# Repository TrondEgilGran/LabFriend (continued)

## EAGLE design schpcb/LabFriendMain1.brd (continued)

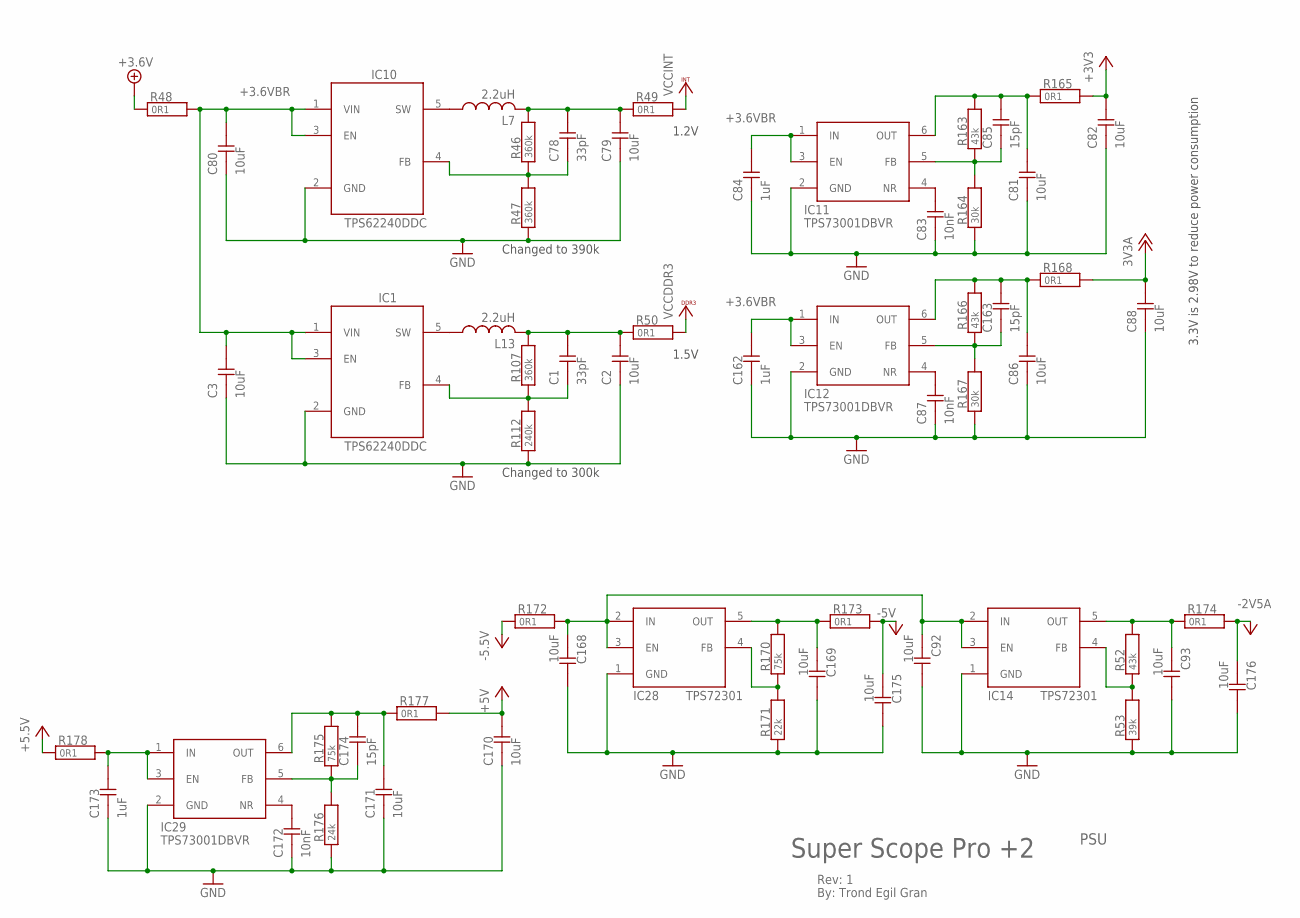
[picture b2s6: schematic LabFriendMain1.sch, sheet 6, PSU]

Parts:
C1, C78: 33pF; 0603
C2, C3, C79, C80, C81, C82, C86, C88, C92, C93, C168, C169, C170, C171, C175, C176: 10uF; 0603
C83, C87, C172: 10nF; 0402
C84, C162, C173: 1uF; 0603
C85, C163, C174: 15pF; 0603
IC1, IC10: TPS62240DDC; SOT23-5L
IC11, IC12, IC29: TPS73001DBVR; SOT23-6L
IC14, IC28: TPS72301; SOT23-5L
L7, L13: 2.2uH; L3216C
R46, R47, R107: 360k; 0603
R48, R49, R50, R165, R168, R172, R173, R174, R177, R178: 0R1; 0603
R52, R163, R166: 43k; 0603
R53: 39k; 0603
R112: 240k; 0603
R164, R167: 30k; 0603
R170, R175: 75k; 0603
R171: 22k; 0603
R176: 24k; 0603

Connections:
3V3A: C88.2, R168.2; also elsewhere on the board
+3.6V: R48.1; also elsewhere on the board
+3.6VBR: C3.2, C80.2, C84.2, C162.2, IC1.1 (VIN), IC1.3 (EN), IC10.1 (VIN), IC10.3 (EN), IC11.1 (IN), IC11.3 (EN), IC12.1 (IN), IC12.3 (EN), R48.2
+3V3: C82.2, R165.2; also elsewhere on the board
+5.5V: R178.1; also elsewhere on the board
+5.5VI: C173.2, IC29.1 (IN), IC29.3 (EN), R178.2
+5V: C170.2, R177.2; also elsewhere on the board
-2.5VI: C93.1, IC14.5 (OUT), R52.2, R174.1
-2V5A: C176.1, R174.2; also elsewhere on the board
-5.5V: R172.1; also elsewhere on the board
-5V: C175.1, R173.2; also elsewhere on the board
GND: C2.1, C3.1, C79.1, C80.1, C81.1, C82.1, C83.1, C84.1, C86.1, C87.1, C88.1, C92.2, C93.2, C162.1, C168.2, C169.2, C170.1, C171.1, C172.1, C173.1, C175.2, C176.2, IC1.2 (GND), IC10.2 (GND), IC11.2 (GND), IC12.2 (GND), IC14.1 (GND), IC28.1 (GND), IC29.2 (GND), R47.1, R53.1, R112.1, R164.1, R167.1, R171.1, R176.1; also elsewhere on the board
unnamed: C83.2, IC11.4 (NR)
unnamed: C78.1, IC10.4 (FB), R46.1, R47.2
unnamed: IC14.4 (FB), R52.1, R53.2
unnamed: IC10.5 (SW), L7.1
unnamed: C92.1, C168.1, IC14.2 (IN), IC14.3 (EN), IC28.2 (IN), IC28.3 (EN), R172.2
unnamed: C78.2, C79.2, L7.2, R46.2, R49.1
unnamed: C87.2, IC12.4 (NR)
unnamed: C1.2, C2.2, L13.2, R50.1, R107.2
unnamed: C1.1, IC1.4 (FB), R107.1, R112.2
unnamed: IC1.5 (SW), L13.1
unnamed: C81.2, C85.2, IC11.6 (OUT), R163.2, R165.1
unnamed: C85.1, IC11.5 (FB), R163.1, R164.2
unnamed: C86.2, C163.2, IC12.6 (OUT), R166.2, R168.1
unnamed: C163.1, IC12.5 (FB), R166.1, R167.2
unnamed: C169.1, IC28.5 (OUT), R170.2, R173.1
unnamed: IC28.4 (FB), R170.1, R171.2
unnamed: C172.2, IC29.4 (NR)
unnamed: C171.2, C174.2, IC29.6 (OUT), R175.2, R177.1
unnamed: C174.1, IC29.5 (FB), R175.1, R176.2
VCCDDR3: R50.2; also elsewhere on the board
VCCINT: R49.2; also elsewhere on the board

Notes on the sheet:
Rev: 1
By: Trond Egil Gran
Super Scope Pro +2
PSU
3.3V is 2.98V to reduce power consumption
1.2V
1.5V
Changed to 300k
Changed to 390k

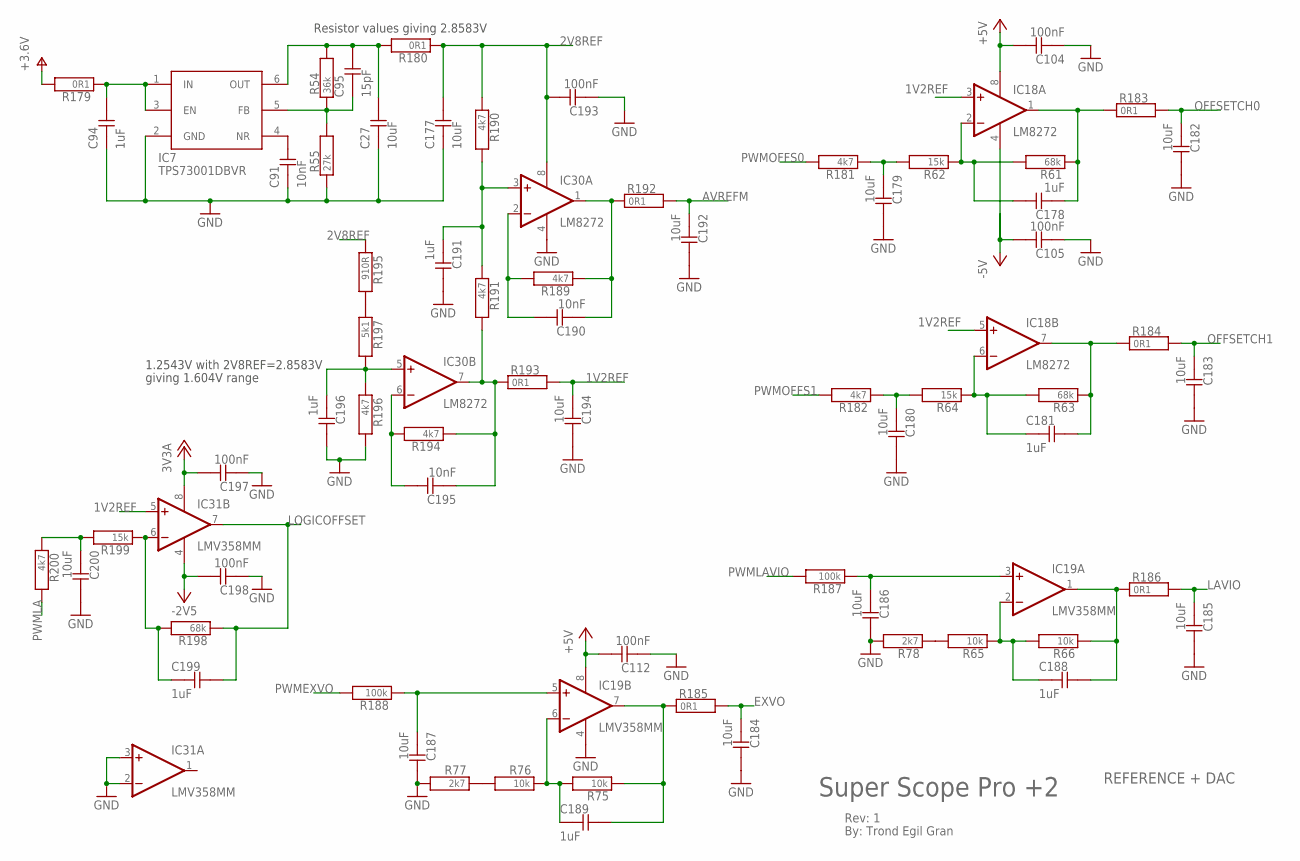
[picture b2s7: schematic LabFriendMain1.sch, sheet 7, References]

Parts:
C27, C177, C179, C180, C182, C183, C184, C185, C186, C187, C192, C194, C200: 10uF; 0603
C91, C190, C195: 10nF; 0402
C94, C178, C181, C188, C189, C191, C196, C199: 1uF; 0603
C95: 15pF; 0603
C104, C105, C112, C193, C197, C198: 100nF; 0402
IC7: TPS73001DBVR; SOT23-6L
IC18, IC30: LM8272; MSOP08
IC19, IC31: LMV358MM; MSOP08
R54: 36k; 0603
R55: 27k; 0603
R61, R63, R198: 68k; 0603
R62, R64, R199: 15k; 0603
R65, R66, R75, R76: 10k; 0603
R77, R78: 2k7; 0603
R179, R180, R183, R184, R185, R186, R192, R193: 0R1; 0603
R181, R182, R189, R190, R191, R194, R196, R200: 4k7; 0603
R187, R188: 100k; 0603
R195: 910R; 0603
R197: 5k1; 0603

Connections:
1V2REF: C194.1, IC18.3 (+IN), IC18.5 (+IN), IC31.5 (+IN), R193.2; also elsewhere on the board
2V8REF: C177.2, C193.2, IC30.8 (V+), R180.1, R190.1, R195.1; also elsewhere on the board
3V3A: C197.2, IC31.8 (V+); also elsewhere on the board
+3.6V: R179.2; also elsewhere on the board
+3.6VI: C94.2, IC7.1 (IN), IC7.3 (EN), R179.1
+5V: C104.2, C112.2, IC18.8 (V+), IC19.8 (V+); also elsewhere on the board
-2V5A: C198.2, IC31.4 (V-); also elsewhere on the board
-5V: C105.2, IC18.4 (V-); also elsewhere on the board
AVREFM: C192.1, R192.2; also elsewhere on the board
EXVO: C184.1, R185.2; also elsewhere on the board
EXVOI: C189.2, IC19.7 (OUT), R75.1, R185.1
GND: C27.1, C91.1, C94.1, C104.1, C105.1, C112.1, C177.1, C179.2, C180.2, C182.2, C183.2, C184.2, C185.2, C186.2, C187.2, C191.2, C192.2, C193.1, C194.2, C196.2, C197.1, C198.1, C200.2, IC7.2 (GND), IC19.4 (V-), IC30.4 (V-), IC31.2 (-IN), IC31.3 (+IN), R55.1, R77.2, R78.2, R196.2; also elsewhere on the board
LAVIO: C185.1, R186.2; also elsewhere on the board
LAVIOI: C188.2, IC19.1 (OUT), R66.1, R186.1
LOGICOFFSET: C199.2, IC31.7 (OUT), R198.1; also elsewhere on the board
unnamed: C191.1, IC30.3 (+IN), R190.2, R191.1
unnamed: C91.2, IC7.4 (NR)
unnamed: C188.1, IC19.2 (-IN), R65.1, R66.2
unnamed: C178.2, IC18.2 (-IN), R61.2, R62.1
unnamed: C27.2, C95.2, IC7.6 (OUT), R54.2, R180.2
unnamed: C181.1, IC18.6 (-IN), R63.2, R64.1
unnamed: C179.1, R62.2, R181.1
unnamed: C180.1, R64.2, R182.1
unnamed: C186.1, IC19.3 (+IN), R187.1
unnamed: C187.1, IC19.5 (+IN), R188.1
unnamed: R76.2, R77.1
unnamed: C95.1, IC7.5 (FB), R54.1, R55.2
unnamed: C189.1, IC19.6 (-IN), R75.2, R76.1
unnamed: R65.2, R78.1
unnamed: R195.2, R197.1
unnamed: C190.1, IC30.1 (OUT), R189.1, R192.1
unnamed: C190.2, IC30.2 (-IN), R189.2
unnamed: C195.1, IC30.7 (OUT), R191.2, R193.1, R194.1
unnamed: C195.2, IC30.6 (-IN), R194.2
unnamed: C196.1, IC30.5 (+IN), R196.1, R197.2
unnamed: C199.1, IC31.6 (-IN), R198.2, R199.1
unnamed: C200.1, R199.2, R200.1
OFFSETCH0: C182.1, R183.2; also elsewhere on the board
OFFSETCH0I: C178.1, IC18.1 (OUT), R61.1, R183.1
OFFSETCH1: C183.1, R184.2; also elsewhere on the board
OFFSETCH1I: C181.2, IC18.7 (OUT), R63.1, R184.1
PWMEXVO: R188.2; also elsewhere on the board
PWMLA: R200.2; also elsewhere on the board
PWMLAVIO: R187.2; also elsewhere on the board
PWMOFFS0: R181.2; also elsewhere on the board
PWMOFFS1: R182.2; also elsewhere on the board

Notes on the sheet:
Rev: 1
By: Trond Egil Gran
Super Scope Pro +2
REFERENCE + DAC
1.2543V with 2V8REF=2.8583V
giving 1.604V range
Resistor values giving 2.8583V

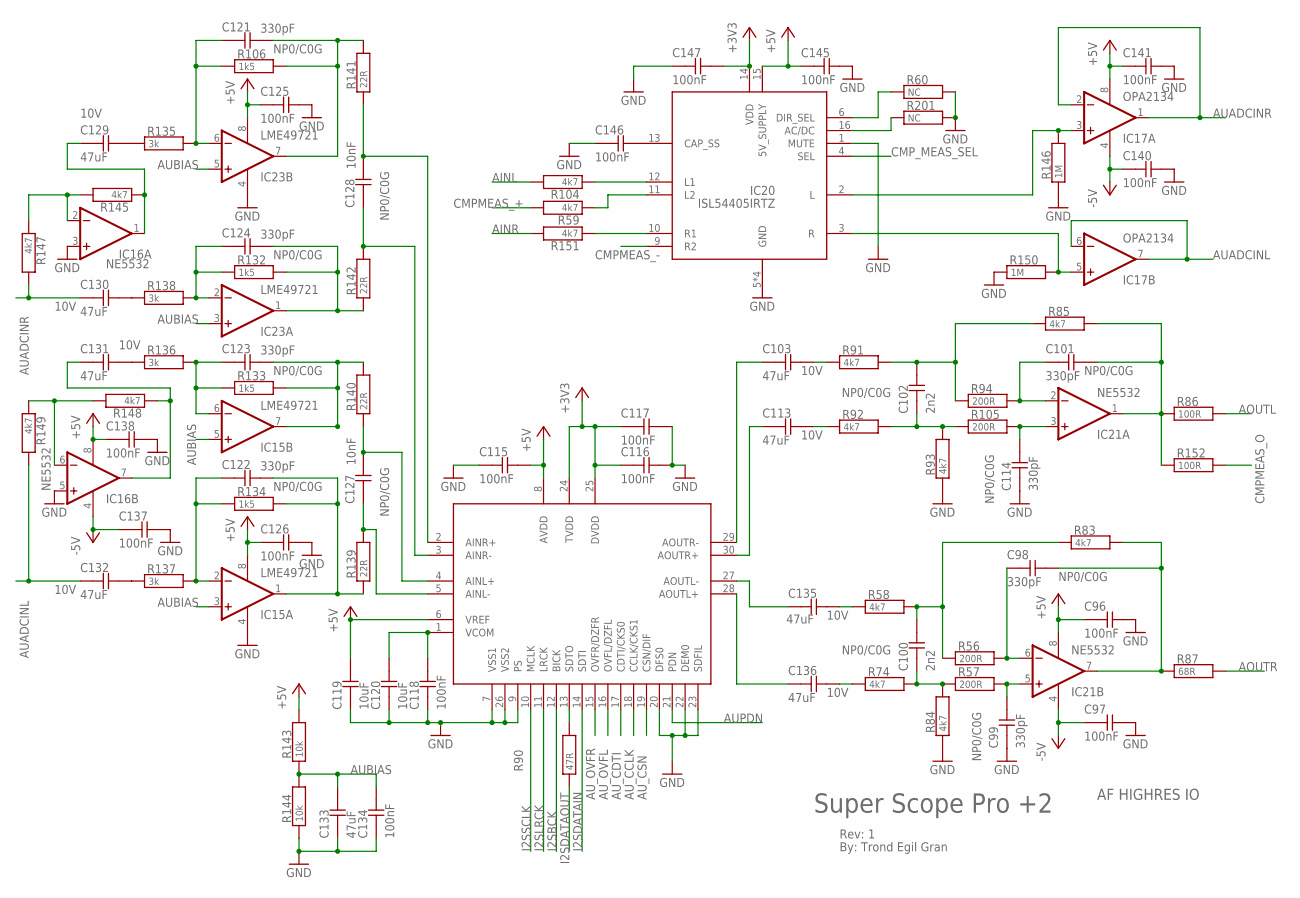
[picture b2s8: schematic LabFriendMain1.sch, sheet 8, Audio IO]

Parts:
C96, C97, C115, C116, C117, C118, C125, C126, C134, C137, C138, C140, C141, C145, C146, C147: 100nF; 0402
C98, C99, C101, C114, C121, C122, C123, C124: 330pF; 0603
C100, C102: 2n2; 0603
C103, C113, C129, C130, C131, C132, C133, C135, C136: 47uF; 1206; VOLTAGE 10V
C119, C120: 10uF; 0603
C127, C128: 10nF; 0603
IC13: AK4621; VSOP30
IC15, IC23: LME49721; SO08
IC16, IC21: NE5532; SO08
IC17: OPA2134; SO08
IC20: ISL54405IRTZ; TQFN3X3
R56, R57, R94, R105: 200R; 0603
R58, R59, R74, R83, R84, R85, R91, R92, R93, R104, R145, R147, R148, R149, R151: 4k7; 0603
R60, R201: NC; 0402
R86, R152: 100R; 0402
R87: 68R; 0603
R90: 47R; 0402
R106, R132, R133, R134: 1k5; 0603
R135, R136, R137, R138: 3k; 0603
R139, R140, R141, R142: 22R; 0603
R143, R144: 10k; 0603
R146, R150: 1M; 0603

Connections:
+3V3: C116.1, C117.1, C147.2, IC13.24 (TVDD), IC13.25 (DVDD), IC20.14 (VDD); also elsewhere on the board
+5V: C96.1, C115.2, C119.2, C125.1, C126.1, C138.1, C141.1, C145.1, IC13.6 (VREF), IC13.8 (AVDD), IC15.8 (V+), IC16.8 (V+), IC17.8 (V+), IC20.15 (5V_SUPPLY), IC21.8 (V+), IC23.8 (V+), R143.2; also elsewhere on the board
-5V: C97.1, C137.1, C140.1, IC16.4 (V-), IC17.4 (V-), IC21.4 (V-); also elsewhere on the board
AINL: R104.2; also elsewhere on the board
AINR: R151.2; also elsewhere on the board
AOUTL: R86.2; also elsewhere on the board
AOUTR: R87.2; also elsewhere on the board
AUADCINL: C132.1, IC17.6 (-IN), IC17.7 (OUT), R149.2
AUADCINR: C130.1, IC17.1 (OUT), IC17.2 (-IN), R147.2
AUBIAS: C133.2, C134.2, IC15.3 (+IN), IC15.5 (+IN), IC23.3 (+IN), IC23.5 (+IN), R143.1, R144.2
AUPDN: IC13.21 (PDN); also elsewhere on the board
AU_CCLK: IC13.18 (CCLK/CKS1); also elsewhere on the board
AU_CDTI: IC13.17 (CDTI/CKS0); also elsewhere on the board
AU_CSN: IC13.19 (CSN/DIF); also elsewhere on the board
AU_OVFL: IC13.16 (OVFL/DZFL); also elsewhere on the board
AU_OVFR: IC13.15 (OVFR/DZFR); also elsewhere on the board
CMPMEAS_+: R59.2; also elsewhere on the board
CMPMEAS_-: IC20.9 (R2); also elsewhere on the board
CMPMEAS_O: R152.2; also elsewhere on the board
CMP_MEAS_SEL: IC20.4 (SEL); also elsewhere on the board
GND: C96.2, C97.2, C99.1, C114.1, C115.1, C116.2, C117.2, C118.1, C119.1, C120.1, C125.2, C126.2, C133.1, C134.1, C137.2, C138.2, C140.2, C141.2, C145.2, C146.1, C147.1, IC13.7 (VSS1), IC13.9 (PS), IC13.20 (DFS0), IC13.22 (DEM0), IC13.23 (SDFIL), IC13.26 (VSS2), IC15.4 (V-), IC16.3 (+IN), IC16.5 (+IN), IC20.1 (MUTE), IC20.5 (GND), IC20.7 (GND), IC20.8 (GND), IC20.GPD (GND), IC23.4 (V-), R60.2, R84.1, R93.1, R144.1, R146.1, R150.1, R201.2; also elsewhere on the board
I2SBCK: IC13.12 (BICK); also elsewhere on the board
I2SDATAIN: IC13.14 (SDTI); also elsewhere on the board
I2SDATAOUT: R90.1; also elsewhere on the board
I2SLRCK: IC13.11 (LRCK); also elsewhere on the board
I2SSCLK: IC13.10 (MCLK); also elsewhere on the board
unnamed: C98.1, IC21.6 (-IN), R56.2
unnamed: C99.2, IC21.5 (+IN), R57.2
unnamed: C98.2, IC21.7 (OUT), R83.2, R87.1
unnamed: C100.2, R56.1, R58.2, R83.1
unnamed: C100.1, R57.1, R74.2, R84.2
unnamed: C135.2, R58.1
unnamed: C136.2, R74.1
unnamed: C101.2, IC21.1 (OUT), R85.2, R86.1, R152.1
unnamed: C101.1, IC21.2 (-IN), R94.2
unnamed: C114.2, IC21.3 (+IN), R105.2
unnamed: C102.2, R85.1, R91.2, R94.1
unnamed: C121.2, IC23.7 (OUT), R106.2, R141.2
unnamed: C102.1, R92.2, R93.2, R105.1
unnamed: C103.2, R91.1
unnamed: C113.2, R92.1
unnamed: C103.1, IC13.29 (AOUTR-)
unnamed: IC13.13 (SDTO), R90.2
unnamed: C113.1, IC13.30 (AOUTR+)
unnamed: C136.1, IC13.28 (AOUTL+)
unnamed: C135.1, IC13.27 (AOUTL-)
unnamed: C121.1, IC23.6 (-IN), R106.1, R135.2
unnamed: C124.2, IC23.1 (OUT), R132.2, R142.1
unnamed: C123.2, IC15.7 (OUT), R133.2, R140.2
unnamed: C118.2, C120.2, IC13.1 (VCOM)
unnamed: C122.2, IC15.1 (OUT), R134.2, R139.1
unnamed: IC20.12 (L1), R104.1
unnamed: C122.1, IC15.2 (-IN), R134.1, R137.2
unnamed: C123.1, IC15.6 (-IN), R133.1, R136.2
unnamed: C124.1, IC23.2 (-IN), R132.1, R138.2
unnamed: C127.2, IC13.4 (AINL+), R140.1
unnamed: C127.1, IC13.5 (AINL-), R139.2
unnamed: C128.1, IC13.3 (AINR-), R142.2
unnamed: C128.2, IC13.2 (AINR+), R141.1
unnamed: C129.2, R135.1
unnamed: C130.2, R138.1
unnamed: C131.2, R136.1
unnamed: C132.2, R137.1
unnamed: C131.1, IC16.7 (OUT), R148.1
unnamed: IC17.5 (+IN), IC20.3 (R), R150.2
unnamed: IC17.3 (+IN), IC20.2 (L), R146.2
unnamed: C146.2, IC20.13 (CAP_SS)
unnamed: C129.1, IC16.1 (OUT), R145.1
unnamed: IC16.2 (-IN), R145.2, R147.1
unnamed: IC16.6 (-IN), R148.2, R149.1
unnamed: IC20.10 (R1), R151.1
unnamed: IC20.11 (L2), R59.1
unnamed: IC20.16 (AC/DC), R201.1
unnamed: IC20.6 (DIR_SEL), R60.1

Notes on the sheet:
Rev: 1
By: Trond Egil Gran
Super Scope Pro +2
AF HIGHRES IO

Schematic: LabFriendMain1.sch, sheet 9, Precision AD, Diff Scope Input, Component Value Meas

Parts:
C139, C148, C150, C204: 100nF; 0402
C201, C202, C203: 10nF; 0402
IC22: 74HC4052D; SO16
IC25: INA331IDGK; MSOP08
IC32: ADS1118IDGSR; MSOP10
R108, R109, R110, R111: 4k7; 0402
R153: 1M; 0603
R154: 100k; 0603
R155: 1k; 0603
R156: 68R; 0603
R202: 91k; 0603
R203: 10k; 0603
R204, R205: 27k; 0603
R206, R207: 22k; 0603
R280: 1k; 0402
R281: 2k2; 0402
SV4: 2x8 Pinheader; MA08-2W
SV5: 3x1 Pinheader; MA03-1

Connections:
+5V: C139.1, C148.1, C204.2, IC22.16 (VCC), IC25.7 (V+), IC25.8 (SD), IC32.8 (VDD); also elsewhere on the board
-5V: C150.2, IC22.7 (VEE); also elsewhere on the board
AINL: SV4.8; also elsewhere on the board
AINR: SV4.7; also elsewhere on the board
AOUTL: SV4.6; also elsewhere on the board
AOUTR: SV4.5; also elsewhere on the board
AUXINCH0: IC25.6 (VOUT), R202.2; also elsewhere on the board
AU_CCLK: IC32.1 (SCLK); also elsewhere on the board
AU_CDTI: IC32.10 (DIN); also elsewhere on the board
AVREFM: IC25.5 (REF), R203.1, R206.2, R207.1; also elsewhere on the board
CMPMEAS_+: R153.1, R154.1, R155.1, R156.1, SV4.1; also elsewhere on the board
CMPMEAS_-: IC22.3 (Y); also elsewhere on the board
CMPMEAS_A: IC22.10 (A); also elsewhere on the board
CMPMEAS_B: IC22.9 (B); also elsewhere on the board
CMPMEAS_EN: IC22.6 (INH); also elsewhere on the board
CMPMEAS_O: IC22.13 (X); also elsewhere on the board
DC_CS: IC32.2 (!CS); also elsewhere on the board
DC_DOUT: R280.1, R281.1; also elsewhere on the board
EXVO: R111.1, SV4.2; also elsewhere on the board
GND: C139.2, C148.2, C150.1, C201.2, C202.2, C203.2, C204.1, IC22.8 (GND), IC25.4 (V-), IC32.3 (GND), R281.2, SV4.3, SV4.4, SV4.9, SV4.10, SV4.12, SV4.13, SV5.2; also elsewhere on the board
HFDAC: SV4.11; also elsewhere on the board
unnamed: C203.1, IC32.4 (AIN0), R108.2
unnamed: C202.1, IC32.5 (AIN1), R109.2
unnamed: C201.1, IC32.6 (AIN2), R110.2
unnamed: R108.1, SV4.15
unnamed: R109.1, SV4.16
unnamed: IC32.7 (AIN3), R111.2
unnamed: R110.1, SV4.14
unnamed: IC22.1 (Y0), IC22.12 (X0), R153.2
unnamed: IC22.5 (Y1), IC22.14 (X1), R154.2
unnamed: IC22.2 (Y2), IC22.15 (X2), R155.2
unnamed: IC22.4 (Y3), IC22.11 (X3), R156.2
unnamed: IC25.1 (RG), R202.1, R203.2
unnamed: IC25.3 (VIN+), R204.2, R207.2
unnamed: IC25.2 (VIN-), R205.2, R206.1
unnamed: R204.1, SV5.3
unnamed: R205.1, SV5.1
unnamed: IC32.9 (DOUT/!DRDY), R280.2

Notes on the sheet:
Rev: 1
By: Trond Egil Gran
Super Scope Pro +2
LS ANALOG IN

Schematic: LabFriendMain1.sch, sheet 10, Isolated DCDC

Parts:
C149: 100pF; 0603
C151, C152: 47pF; 0603
C153, C154, C155, C156, C160: 100nF; 0402
C157, C158, C159, C161: 100uF; CT6032
D1, D2, D3, D4, D5, D6: SK14; DO214AC
IC24: 74HC00D; SO14
IC27: 74HCT132D; SO14
Q2, Q3: FDN335N; SOT23
R157, R158: 10k; 0603
R159, R160: 1k5; 0603
R161, R162: 150R; 0603
T1: EFD15DCDCPM5P33EFD15; B66414-W1008-D1

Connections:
+3.6V: C160.1, C161.+, D5.C, D6.C; also elsewhere on the board
+5.5V: C156.1, C157.+, D1.C, D2.C; also elsewhere on the board
+UB: C153.2, C154.2, C159.+, IC24.14 (VCC), IC27.14 (VCC), T1.2 (P1M); also elsewhere on the board
-5.5V: C155.2, C158.-, D3.A, D4.A; also elsewhere on the board
GND: C155.1, C156.2, C157.-, C158.+, C160.2, C161.-, T1.4 (SM); also elsewhere on the board
GNDIO: C151.1, C152.1, C153.1, C154.1, C159.-, IC24.7 (GND), IC27.7 (GND), Q2.2 (S), Q3.2 (S); also elsewhere on the board
unnamed: IC27.1 (I0), IC27.2 (I1), R157.1
unnamed: IC24.4 (I0), IC24.5 (I1), IC27.3 (O)
unnamed: C149.1, R157.2, R158.1
unnamed: C149.2, IC24.1 (I0), IC24.2 (I1), IC24.6 (O)
unnamed: IC24.3 (O), IC27.4 (I0), IC27.5 (I1), IC27.12 (I0), R158.2, R160.1
unnamed: C151.2, IC27.13 (I1), R160.2
unnamed: IC27.6 (O), IC27.9 (I0), R159.1
unnamed: C152.2, IC27.10 (I1), R159.2
unnamed: IC24.9 (I0), IC24.10 (I1), IC27.8 (O)
unnamed: IC24.12 (I0), IC24.13 (I1), IC27.11 (O)
unnamed: IC24.11 (O), R161.1
unnamed: IC24.8 (O), R162.1
unnamed: Q3.1 (G), R162.2
unnamed: D2.A, D3.C, T1.8 (S1P)
unnamed: D1.A, D4.C, T1.7 (S1N)
unnamed: Q2.3 (D), T1.1 (P1P)
unnamed: Q2.1 (G), R161.2
unnamed: Q3.3 (D), T1.3 (P1N)
unnamed: D5.A, T1.5 (S2P)
unnamed: D6.A, T1.6 (S2N)

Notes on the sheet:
Changed to 82p

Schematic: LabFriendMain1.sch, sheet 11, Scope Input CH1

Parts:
C205: 10uF; 0603
C206, C207, C208, C209, C210, C218, C219, C220, C221, C225, C226, C227: 100nF; 0402
C211: 100nF; 0603; VOLTAGE 50V
C212, C214, C217, C222, C223: 12pF; 0603
C213, C216: 6/30; CTRIMTZBX4
C215: 220pF; 0603
C224: 100uF; 1206
C228, C229: 1pF; 0603
IC33: ADA4853-3RU; SO14
IC34, IC35: 4052D; SO16
IC36: OPA2354; MSOP08
IC37: 74HC595D; SO16
K1, K2: G6K-2F-Y
L12: 1uH; L3216C
R208: 200R; 0603
R209: 30R; 0603
R210: 20R; 0603
R211, R214, R217, R237, R239: 22R; 0603
R212, R215, R216, R229, R230, R238: 300R; 0603
R213: 100R; 0603
R218, R219, R220: 10k; 0603
R221, R222: 30k; 0603
R223, R224: 470k; 0603
R225: 51k; 0603
R226: 39k; 0603
R227: 910k; 0603
R228: 1k; 0603
R231: 7R5; 0603
R232, R233, R234, R235, R236: 10R; 0603
R240: 1R; 0603
R241: 100R; 0402
R242, R243: 47R; 0603
T2, T3, T4, T8: BC850; SOT23
T5, T6, T7, T9: BC856ASMD; SOT23-BEC
X2: 31-5431-10RFX; AMP_227161

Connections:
3V3A: C218.2, IC36.8 (V+); also elsewhere on the board
+5V: C205.2, C206.2, C208.2, C210.2, C221.2, IC33.4 (V+), IC34.16 (VCC), IC35.16 (VCC), IC37.10 (SCL), IC37.16 (VCC), R232.2; also elsewhere on the board
-2V5A: C207.1, C209.1, C219.1, IC34.7 (VEE), IC35.7 (VEE), IC36.4 (V-); also elsewhere on the board
ATTRL+: IC37.1 (QB), R234.2
ATTRL-: IC37.15 (QA), R236.1
AUXIN: IC34.11 (X3); also elsewhere on the board
AUXOUT: R239.2
AVREFM: C225.1, C226.1, C227.1, R210.1, R213.1, R216.1, R218.1, R219.1, R220.1; also elsewhere on the board
DCRL+: IC37.3 (QD), R235.2
DCRL-: IC37.2 (QC), R233.1
GMUXA: IC34.10 (A), IC37.4 (QE)
GMUXB: IC34.9 (B), IC37.5 (QF)
GMUXC: IC35.10 (A), IC37.6 (QG)
GMUXD: IC35.9 (B), IC37.7 (QH)
GND: C205.1, C206.1, C207.2, C208.1, C209.2, C210.1, C212.1, C213.2 (A), C215.1, C216.2 (A), C218.1, C219.2, C220.1, C221.1, C224.2, C225.2, C226.2, C227.2, IC33.1 (!POWERDOWN), IC33.2 (!POWERDOWN), IC33.3 (!POWERDOWN), IC33.11 (V-), IC34.6 (INH), IC34.8 (GND), IC35.6 (INH), IC35.8 (GND), IC37.8 (GND), IC37.13 (G), R224.1, R228.1, R240.1, T5.C, T6.C, T7.C, T9.C; also elsewhere on the board
unnamed: IC33.6 (IN-), R208.1, R209.2
unnamed: IC33.7 (OUT), R208.2, R211.2
unnamed: R209.1, R210.2
unnamed: IC33.9 (IN-), R212.1, R213.2
unnamed: IC33.13 (IN-), R215.1, R216.2
unnamed: IC33.14 (OUT), R215.2, R217.2
unnamed: IC33.5 (IN+), IC34.12 (X0), IC35.5 (Y1), IC35.15 (X2), R220.2, R231.1
unnamed: IC33.8 (OUT), R212.2, R214.2
unnamed: IC35.1 (Y0), IC35.11 (X3), R211.1
unnamed: IC33.12 (IN+), IC35.13 (X), R219.2
unnamed: IC34.14 (X1), IC35.12 (X0), R214.1
unnamed: IC34.15 (X2), R217.1
unnamed: IC33.10 (IN+), IC35.3 (Y), R218.2
unnamed: C211.2, K1.3, R241.1
unnamed: C211.1, K1.2 (O), K2.3
unnamed: R221.2, R223.1
unnamed: C212.2, C214.1, C228.1, R221.1, R222.2, R242.2
unnamed: R222.1, R224.2
unnamed: C214.2, C223.2, C228.2, K2.4 (S), R223.2
unnamed: R225.2, R227.1
unnamed: R226.1, R228.2
unnamed: C217.2, C222.2, C229.2, K2.2 (O), R227.2
unnamed: IC36.2 (-IN), R229.1, R230.2
unnamed: IC36.1 (OUT), R229.2, R231.2
unnamed: IC34.13 (X), IC36.5 (+IN)
unnamed: C224.1, R232.1, T2.3 (C), T3.3 (C), T4.3 (C), T8.3 (C)
unnamed: K1.8 (-), T3.2 (E), T6.E
unnamed: K1.1 (+), T2.2 (E), T5.E
unnamed: R235.1, T2.1 (B), T5.B
unnamed: R233.2, T3.1 (B), T6.B
unnamed: K2.1 (+), T4.2 (E), T7.E
unnamed: K2.8 (-), T8.2 (E), T9.E
unnamed: R234.1, T4.1 (B), T7.B
unnamed: R236.2, T8.1 (B), T9.B
unnamed: IC36.7 (OUT), R237.2, R238.2, R239.1
unnamed: IC36.3 (+IN), K2.6
unnamed: C216.1 (E), C222.1
unnamed: C213.1 (E), C223.1
unnamed: IC36.6 (-IN), R238.1
unnamed: C220.2, L12.1, R230.1
unnamed: C215.2, C217.1, C229.1, R225.1, R226.2, R243.2
unnamed: R240.2, X2.2
unnamed: R241.2, X2.1
unnamed: K2.5 (S), R242.1
unnamed: K2.7 (O), R243.1
OFFSETCH1: L12.2; also elsewhere on the board
OUTPUTCH1: R237.1; also elsewhere on the board
SPICHAIN: IC37.9 (QH*); also elsewhere on the board
SPICLK: IC37.11 (SCK); also elsewhere on the board
SPICS: IC37.12 (RCK); also elsewhere on the board
SPIDI: IC37.14 (SER); also elsewhere on the board

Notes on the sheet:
SPIDI SPICLK SPICS SPICHAIN
OUTPUT AUXOUT AUXIN +5V -2.5VA +3VA

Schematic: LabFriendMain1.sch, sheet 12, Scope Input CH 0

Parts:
C230: 10uF; 0603
C231, C232, C233, C234, C235, C243, C244, C245, C246, C250, C251, C252: 100nF; 0402
C236: 100nF; 0603; VOLTAGE 50V
C237, C239, C242, C247, C248: 12pF; 0603
C238, C241: 6/30; CTRIMTZBX4
C240: 220pF; 0603
C249: 100uF; 1206
C253, C254: 1pF; 0603
IC38: ADA4853-3RU; SO14
IC39, IC40: 4052D; SO16
IC41: OPA2354; MSOP08
IC42: 74HC595D; SO16
K3, K4: G6K-2F-Y
L14: 1uH; L3216C
R244: 200R; 0603
R245: 30R; 0603
R246: 20R; 0603
R247, R250, R253, R273, R275, R278, R279: 22R; 0603
R248, R251, R252, R265, R266, R274: 300R; 0603
R249, R277: 100R; 0603
R254, R255, R256: 10k; 0603
R257, R258: 30k; 0603
R259, R260: 470k; 0603
R261: 130k; 0603
R262: 47k; 0603
R263: 820k; 0603
R264: 3k; 0603
R267: 7R5; 0603
R268, R269, R270, R271, R272: 10R; 0603
R276: 1R; 0603
T10, T11, T14, T16: BC850; SOT23
T12, T13, T15, T17: BC856ASMD; SOT23-BEC
X3: 31-5431-10RFX; AMP_227161

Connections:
3V3A: C243.2, IC41.8 (V+); also elsewhere on the board
+5V: C230.2, C231.2, C233.2, C235.2, C246.2, IC38.4 (V+), IC39.16 (VCC), IC40.16 (VCC), IC42.10 (SCL), IC42.16 (VCC), R268.2; also elsewhere on the board
-2V5A: C232.1, C234.1, C244.1, IC39.7 (VEE), IC40.7 (VEE), IC41.4 (V-); also elsewhere on the board
ATTRL+B: IC42.1 (QB), R270.2
ATTRL-B: IC42.15 (QA), R272.1
AUXIN: R275.2; also elsewhere on the board
AUXINCH0: IC39.11 (X3); also elsewhere on the board
AVREFM: C250.1, C251.1, C252.1, R246.1, R249.1, R252.1, R254.1, R255.1, R256.1; also elsewhere on the board
DCRL+B: IC42.3 (QD), R271.2
DCRL-B: IC42.2 (QC), R269.1
GMUXAB: IC39.10 (A), IC42.4 (QE)
GMUXBB: IC39.9 (B), IC42.5 (QF)
GMUXCB: IC40.10 (A), IC42.6 (QG)
GMUXDB: IC40.9 (B), IC42.7 (QH)
GND: C230.1, C231.1, C232.2, C233.1, C234.2, C235.1, C237.1, C238.2 (A), C240.1, C241.2 (A), C243.1, C244.2, C245.1, C246.1, C249.2, C250.2, C251.2, C252.2, IC38.1 (!POWERDOWN), IC38.2 (!POWERDOWN), IC38.3 (!POWERDOWN), IC38.11 (V-), IC39.6 (INH), IC39.8 (GND), IC40.6 (INH), IC40.8 (GND), IC42.8 (GND), IC42.13 (G), R260.1, R264.1, R276.1, T12.C, T13.C, T15.C, T17.C; also elsewhere on the board
unnamed: IC38.6 (IN-), R244.1, R245.2
unnamed: IC38.7 (OUT), R244.2, R247.2
unnamed: R245.1, R246.2
unnamed: IC38.9 (IN-), R248.1, R249.2
unnamed: IC38.13 (IN-), R251.1, R252.2
unnamed: IC38.14 (OUT), R251.2, R253.2
unnamed: IC38.5 (IN+), IC39.12 (X0), IC40.5 (Y1), IC40.15 (X2), R256.2, R267.1
unnamed: IC38.8 (OUT), R248.2, R250.2
unnamed: IC40.1 (Y0), IC40.11 (X3), R247.1
unnamed: IC38.12 (IN+), IC40.13 (X), R255.2
unnamed: IC39.14 (X1), IC40.12 (X0), R250.1
unnamed: IC39.15 (X2), R253.1
unnamed: IC38.10 (IN+), IC40.3 (Y), R254.2
unnamed: C236.2, K3.3, R277.1
unnamed: C236.1, K3.2 (O), K4.3
unnamed: R257.2, R259.1
unnamed: C237.2, C239.1, C253.1, R257.1, R258.2, R278.2
unnamed: R258.1, R260.2
unnamed: C239.2, C248.2, C253.2, K4.4 (S), R259.2
unnamed: R261.2, R263.1
unnamed: R262.1, R264.2
unnamed: C242.2, C247.2, C254.2, K4.2 (O), R263.2
unnamed: IC41.2 (-IN), R265.1, R266.2
unnamed: IC41.1 (OUT), R265.2, R267.2
unnamed: IC39.13 (X), IC41.5 (+IN)
unnamed: C249.1, R268.1, T10.3 (C), T11.3 (C), T14.3 (C), T16.3 (C)
unnamed: K3.8 (-), T11.2 (E), T13.E
unnamed: K3.1 (+), T10.2 (E), T12.E
unnamed: R271.1, T10.1 (B), T12.B
unnamed: R269.2, T11.1 (B), T13.B
unnamed: K4.1 (+), T14.2 (E), T15.E
unnamed: K4.8 (-), T16.2 (E), T17.E
unnamed: R270.1, T14.1 (B), T15.B
unnamed: R272.2, T16.1 (B), T17.B
unnamed: IC41.7 (OUT), R273.2, R274.2, R275.1
unnamed: IC41.3 (+IN), K4.6
unnamed: C241.1 (E), C247.1
unnamed: C238.1 (E), C248.1
unnamed: IC41.6 (-IN), R274.1
unnamed: C245.2, L14.1, R266.1
unnamed: C240.2, C242.1, C254.1, R261.1, R262.2, R279.2
unnamed: R276.2, X3.2
unnamed: R277.2, X3.1
unnamed: K4.5 (S), R278.1
unnamed: K4.7 (O), R279.1
OFFSETCH0: L14.2; also elsewhere on the board
OUTPUTCH0: R273.1; also elsewhere on the board
SPICHAIN: IC42.14 (SER); also elsewhere on the board
SPICHAINB: IC42.9 (QH*)
SPICLK: IC42.11 (SCK); also elsewhere on the board
SPICS: IC42.12 (RCK); also elsewhere on the board

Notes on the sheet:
SPIDI SPICLK SPICS SPICHAIN
OUTPUT AUXOUT AUXIN +5V -2.5VA +3VA

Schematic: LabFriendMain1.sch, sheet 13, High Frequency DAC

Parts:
C255, C256: 100nF; 0402
IC43: LM321MF; SOT23-5
IC44: 74HC595D; SO16
R282: 50R; 0603
R283, R285, R292, R293, R294, R295, R296, R297, R298: 1k6; 0603
R284, R286, R287, R288, R289, R290, R291: 820R; 0603
R299: 39R; 0603
R300: 300R; 0603

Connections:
+5V: C255.1, C256.1, IC43.5 (V+), IC44.10 (SCL), IC44.16 (VCC); also elsewhere on the board
GND: C255.2, C256.2, IC43.2 (V-), IC44.8 (GND), IC44.13 (G), R299.1; also elsewhere on the board
HFDAC: R282.2; also elsewhere on the board
HFDAC_CLK: IC44.11 (SCK); also elsewhere on the board
HFDAC_CS: IC44.12 (RCK); also elsewhere on the board
HFDAC_DI: IC44.14 (SER); also elsewhere on the board
unnamed: R284.1, R285.1, R286.2
unnamed: R286.1, R287.2, R293.1
unnamed: R287.1, R288.2, R294.1
unnamed: R288.1, R289.2, R295.1
unnamed: R289.1, R290.2, R296.1
unnamed: R290.1, R291.2, R297.1
unnamed: R291.1, R292.2, R298.1
unnamed: R292.1, R299.2
unnamed: IC43.1 (+IN), R283.2, R284.2
unnamed: IC44.15 (QA), R283.1
unnamed: IC44.1 (QB), R285.2
unnamed: IC44.2 (QC), R293.2
unnamed: IC44.3 (QD), R294.2
unnamed: IC44.4 (QE), R295.2
unnamed: IC44.5 (QF), R296.2
unnamed: IC44.6 (QG), R297.2
unnamed: IC44.7 (QH), R298.2
unnamed: IC43.3 (-IN), R300.1
unnamed: IC43.4 (OUT), R282.1, R300.2

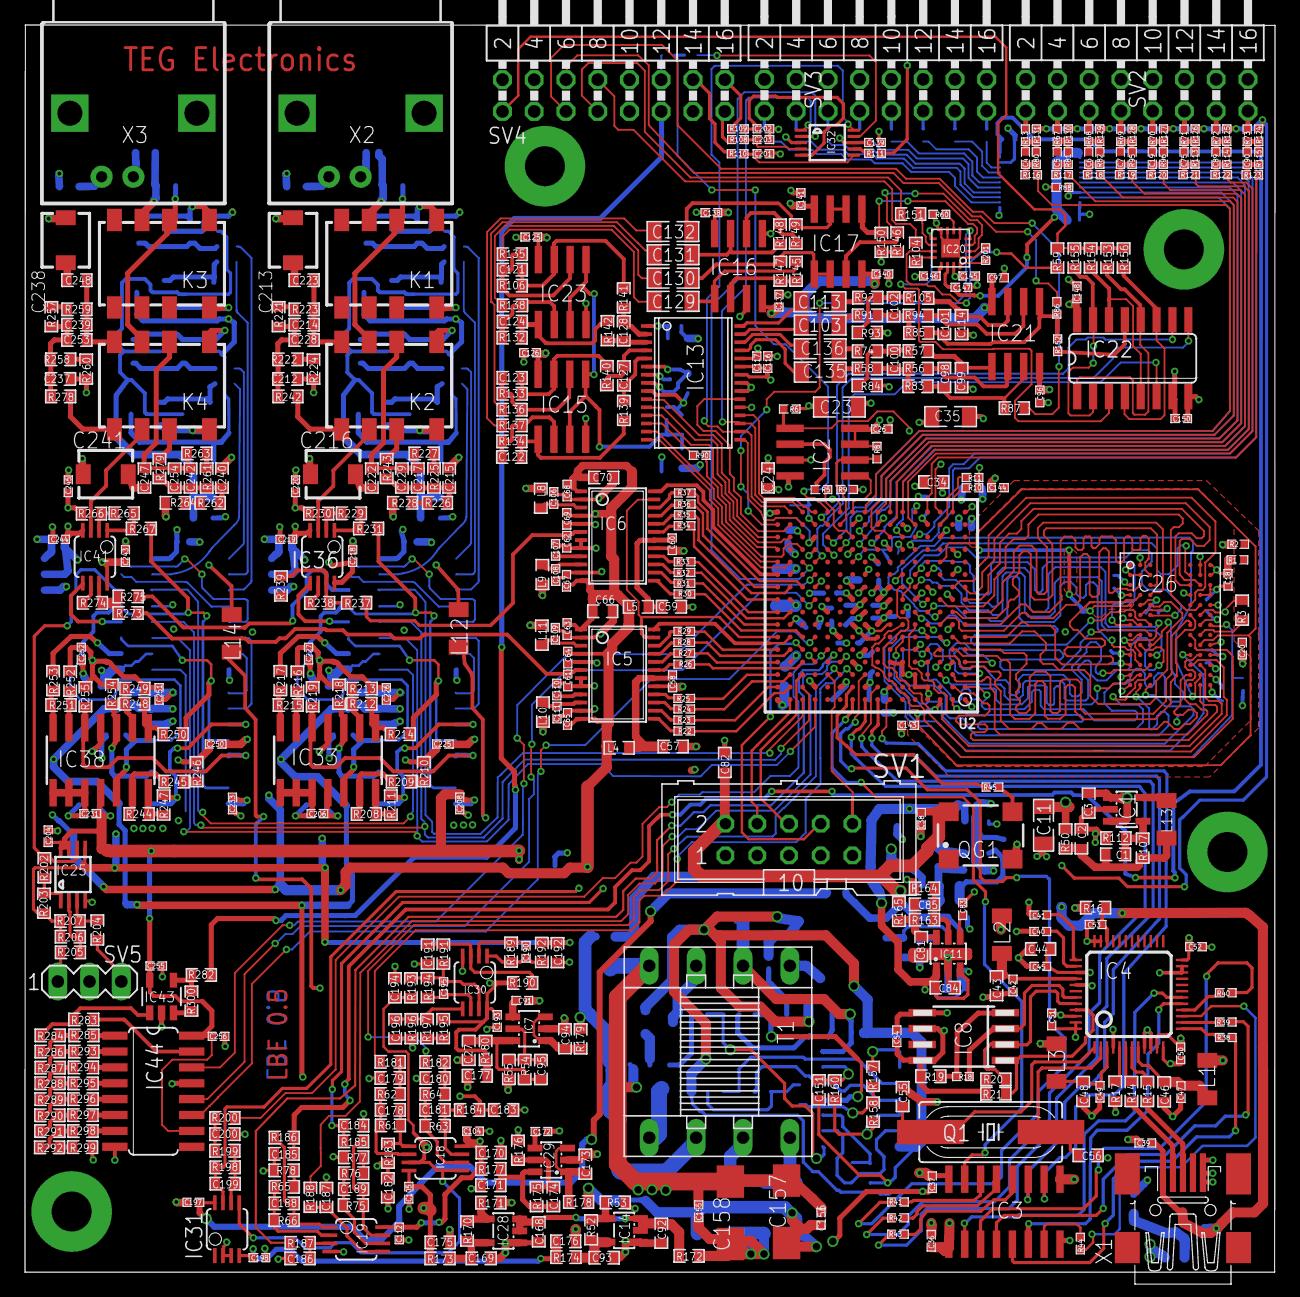
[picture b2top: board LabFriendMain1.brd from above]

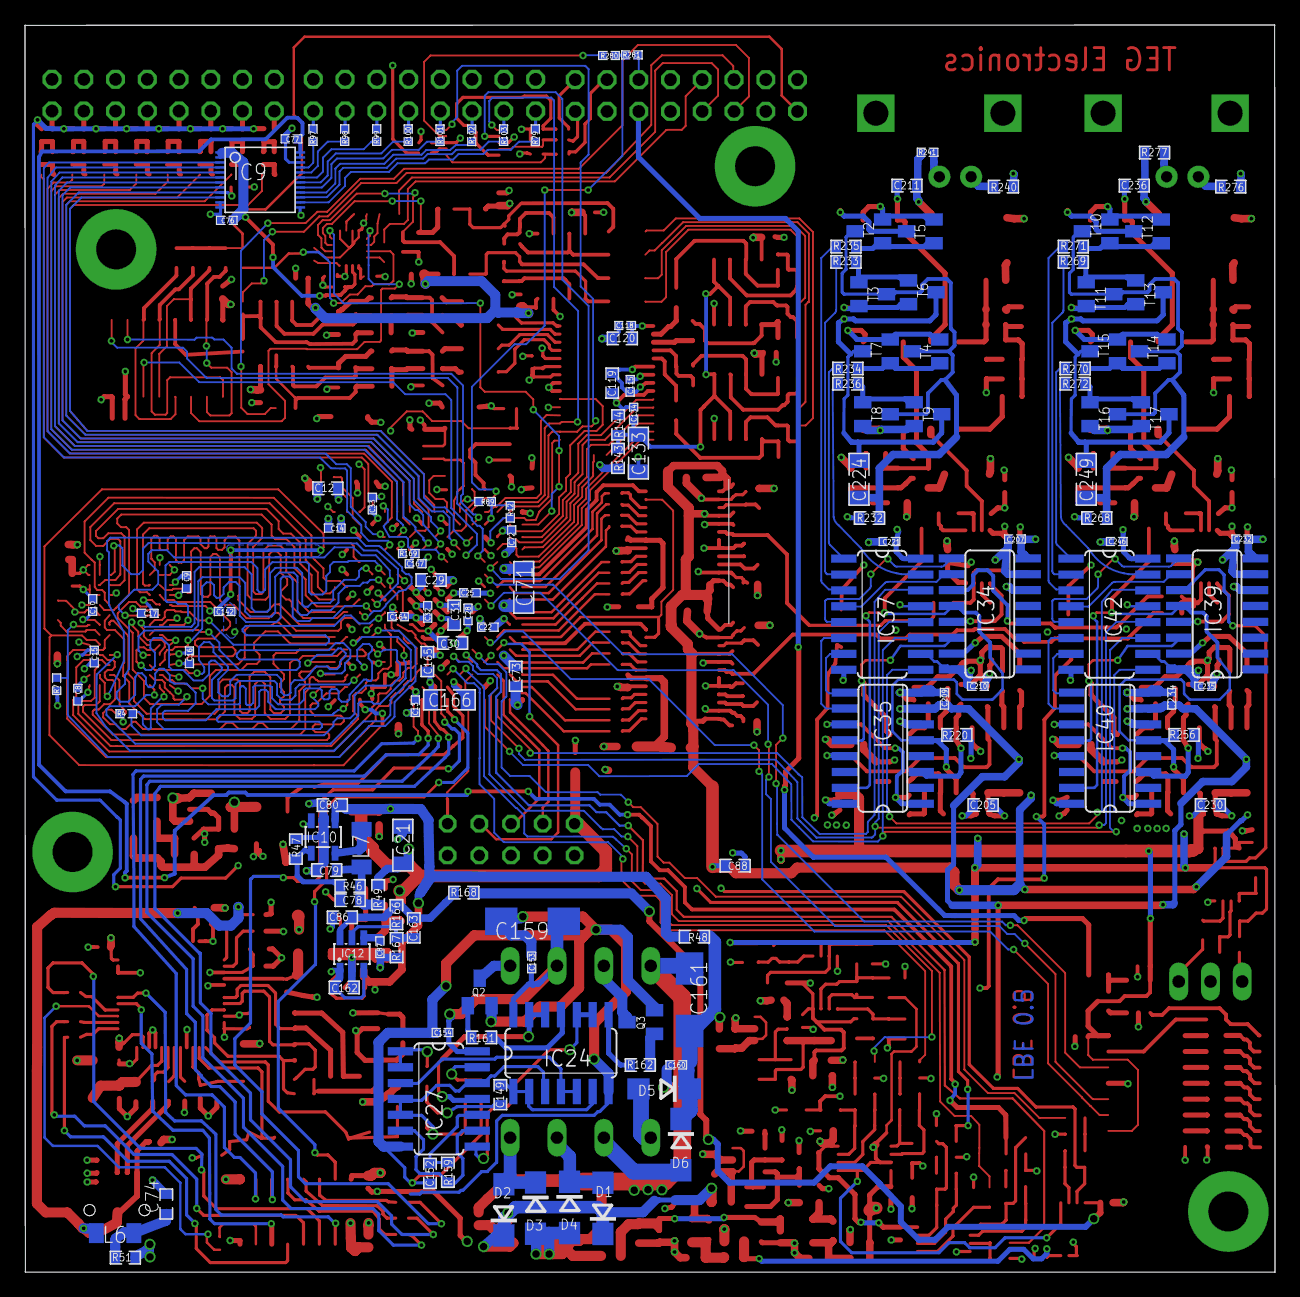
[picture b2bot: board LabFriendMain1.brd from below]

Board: 4 copper layers, 100.0 x 99.8 mm, 654 parts (145 on the bottom side), 517 nets.
